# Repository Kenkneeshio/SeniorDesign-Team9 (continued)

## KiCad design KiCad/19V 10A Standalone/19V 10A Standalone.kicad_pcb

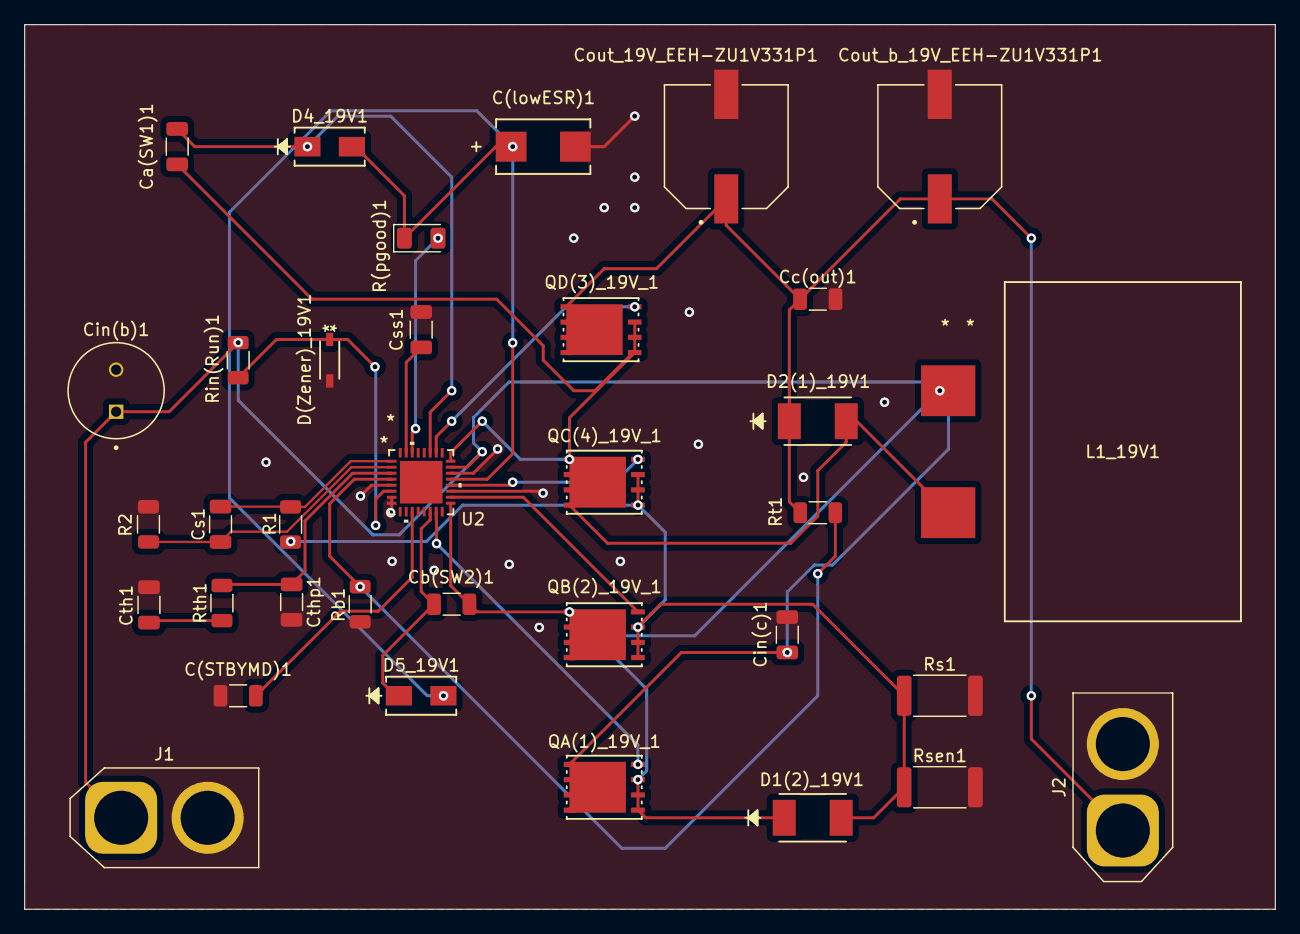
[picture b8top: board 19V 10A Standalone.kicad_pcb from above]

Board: 2 copper layers, 104.1 x 73.7 mm, 35 parts (0 on the bottom side), 22 nets.

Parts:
C(STBYMD)1: 0.001u; C_1206_3216Metric
C(lowESR)1: 4.7u; CAPMP7.6X4.3_3.1N_KEM
Ca(SW1)1: 0.22u; C_1206_3216Metric
Cb(SW2)1: 0.22u; C_1206_3216Metric
Cc(out)1: 47u; C_1206_3216Metric
Cin(b)1: 270u; LargeCAPSCAPPRD350W60D800H1200
Cin(c)1: 10u; C_1206_3216Metric
Cout_19V_EEH-ZU1V331P1: 330u; CAP_EEHZU1V331P
Cout_b_19V_EEH-ZU1V331P1: 330u; CAP_EEHZU1V331P
Cs1: 100p; C_1206_3216Metric
Css1: 0.001u; C_1206_3216Metric
Cth1: 10000p; C_1206_3216Metric
Cthp1: 47p; C_1206_3216Metric
D1(2)_19V1, D2(1)_19V1: SD2114S040S8R0; SD2114_AVX
D4_19V1, D5_19V1: D_Schottky_B340AE-13; CR_SMA_320-340AE_DIO
D(Zener)_19V1: D_Zener_BZT52C4V7-13-F; SOD123_DIO
J1: Conn_01x02_Socket; AMASS_XT60-M_1x02_P7.20mm_Vertical
J2: Conn_01x02_Socket; AMASS_XT60-F_1x02_P7.20mm_Vertical
L1_19V1: 6.8u Wurth 74436410680; IND_410680_WRE
QA(1)_19V_1: BSC009NE2LS5IATMA1; PG-TDSON-8_INF_modified_ken
QB(2)_19V_1: BSC009NE2LS5IATMA1; PG-TDSON-8_INF_modified_ken
QC(4)_19V_1: BSC009NE2LS5IATMA1; PG-TDSON-8_INF_modified_ken
QD(3)_19V_1: BSC009NE2LS5IATMA1; PG-TDSON-8_INF_modified_ken
R1, R2: 100; R_1206_3216Metric
R(pgood)1: 100k; LED_1206_3216Metric
Rb1: 4.3K; R_1206_3216Metric
Rin(Run)1: 51K; R_1206_3216Metric
Rs1: 6m; R_2512_6332Metric
Rsen1: 6m; R_2512_6332Metric
Rt1: 100K; R_1206_3216Metric
Rth1: 124K; R_1206_3216Metric
U2: LTC3780EUH-TRPBF; QFN-32_UH_LIT

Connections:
/BG1: QC(4)_19V_1.4, U2.20 (BG1)
/BG2: QB(2)_19V_1.4, U2.18 (BG2)
/BOOST1: Ca(SW1)1.1, D4_19V1.1 (K), U2.27 (BOOST1)
/BOOST2: Cb(SW2)1.2, D5_19V1.1 (K), U2.14 (BOOST2)
/INTVCC: C(lowESR)1.1, D4_19V1.2 (A), D5_19V1.2 (A), R(pgood)1.1, U2.21 (INTVCC)
/ITH: Cthp1.1, Rth1.2, U2.3 (ITH)
/PGOOD: R(pgood)1.2, U2.30 (PGOOD)
/Rsense: D1(2)_19V1.2, QB(2)_19V_1.1, QB(2)_19V_1.2, QB(2)_19V_1.3, QC(4)_19V_1.1, QC(4)_19V_1.2, QC(4)_19V_1.3, R1.1, Rs1.1, Rsen1.1
/Run: D(Zener)_19V1.1 (K), Rin(Run)1.2, U2.6 (RUN)
/SENSE+: Cs1.2, R1.2, U2.1 (SENSE+)
/SENSE-: Cs1.1, R2.1, U2.2 (SENSE-)
/SS: Css1.2, U2.31 (SS)
/STBYMD: C(STBYMD)1.1, U2.11 (STBYMD)
/SW1: Ca(SW1)1.2, D2(1)_19V1.2, L1_19V1.2, QC(4)_19V_1.5, QC(4)_19V_1.6, QC(4)_19V_1.7, QC(4)_19V_1.8, QD(3)_19V_1.1, QD(3)_19V_1.2, QD(3)_19V_1.3, U2.24 (SW1)
/SW2: Cb(SW2)1.1, D1(2)_19V1.1, L1_19V1.1, QA(1)_19V_1.1, QA(1)_19V_1.2, QA(1)_19V_1.3, QB(2)_19V_1.5, QB(2)_19V_1.6, QB(2)_19V_1.7, QB(2)_19V_1.8, U2.17 (SW2)
/TG1: QD(3)_19V_1.4, U2.26 (TG1)
/TG2: QA(1)_19V_1.4, U2.15 (TG2)
/VOSENSE: Rb1.1, Rt1.2, U2.4 (VOSENSE)
/Vin: Cin(b)1.1, Cin(c)1.1, J1.1, QA(1)_19V_1.5, QA(1)_19V_1.6, QA(1)_19V_1.7, QA(1)_19V_1.8, Rin(Run)1.1, U2.23 (VIN)
/Vout: Cc(out)1.1, Cout_19V_EEH-ZU1V331P1.1, Cout_b_19V_EEH-ZU1V331P1.1, D2(1)_19V1.1, J2.1, QD(3)_19V_1.5, QD(3)_19V_1.6, QD(3)_19V_1.7, QD(3)_19V_1.8, Rt1.1
GND: C(STBYMD)1.2, C(lowESR)1.2, Cc(out)1.2, Cin(b)1.2, Cin(c)1.2, Cout_19V_EEH-ZU1V331P1.2, Cout_b_19V_EEH-ZU1V331P1.2, Css1.1, Cth1.2, Cthp1.2, D(Zener)_19V1.2 (A), J1.2, J2.2, R2.2, Rb1.2, Rs1.2, Rsen1.2, U2.5 (SGND), U2.7 (FCB), U2.8 (PLLFLTR), U2.19 (PGND), U2.22 (EXTVCC)
unnamed: Cth1.1, Rth1.1

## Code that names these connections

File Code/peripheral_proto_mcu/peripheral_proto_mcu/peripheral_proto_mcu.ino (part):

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#include <OneWire.h>           // used for temperature sensor one wire
#include <DallasTemperature.h> // temperature sensor library

#define ONE_WIRE_BUS 5 // THE DIGITAL PIN THAT THE TEMPERATURE SENSORS ARE CONNECTED TO
//////////////////////////////
// FINAL BOARD PINS
#define VOLTAGE0_PIN A0
#define VOLTAGE1_PIN A1
#define CURRENT0_PIN A2
#define CURRENT1_PIN A3
/////////////////////////////

//////////////////////////////
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// #define VOLTAGE0_PIN A0
// #define VOLTAGE1_PIN A2
// #define CURRENT0_PIN A1
// #define CURRENT1_PIN A3
/////////////////////////////

//////////////////////////////////////////////////////////
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
  if (millis() > millis_ctr)
  {
    presentCurrent0 = ADC2Current(analogRead(CURRENT0_PIN));    // read analog value from adc, and pass to ADC2Current to convert into a real current
    presentVoltage0 = ADC2Voltage(analogRead(VOLTAGE0_PIN), 1); // read analog value from adc, and pass to ADC2Voltage to convert into a real voltage
    presentCurrent1 = ADC2Current(analogRead(CURRENT1_PIN));    // read analog value from adc, and pass to ADC2Current to convert into a real current
    presentVoltage1 = ADC2Voltage(analogRead(VOLTAGE1_PIN), 2); // read analog value from adc, and pass to ADC2Voltage to convert into a real voltage
    
    CollectTemperatureInformation();                            // call the temperature collecting function
    CheckBattery1Voltage(millis_ctr);                           // call the function to check battery one's health
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
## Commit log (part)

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2023-05-06 cleanup
2023-05-06 gitignore zip
2023-05-06 test
2023-05-12 .zip??
2023-05-12 gitignore
2023-05-12 Add MCU to the root Kicad
2023-05-12 Fixed 5V reg footprint
2023-05-12 Add Note for +5V label on 5V Buck
2023-05-12 5V Buck Schematic and Some Components
2023-05-12 Updfates
2023-05-12 Net listed and attacked outline components
2023-05-12 Changed footprints on my end only
2023-05-12 update for layout before 1 H break
2023-05-13 Layout Updates
2023-05-13 VIA FUN
2023-05-13 Load Sharing Traces
2023-05-13 Fixed Footprint/Symbol Paths and 19V Boost Footprint
2023-05-13 so many updates
2023-05-13 All Footprints Load from Mechatronics Folder
2023-05-13 My Load Sharing Group
2023-05-13 LTPowerCad files with BSC009NE2LS5I on all mosfets
    BSC009NE2LS5I
2023-05-14 Completed Load Sharing Circuit PCB
2023-05-14 Deleted 12 and 5 V. 19V updated
2023-05-14 Corrceted 19V components
2023-05-14 Fully Updated 19V SCh
2023-05-14 Added Voltmeter
2023-05-14 Major Changes
2023-05-14 Repaired root grid
2023-05-14 Repaired Grid root
2023-05-14 fixed SW1
2023-05-14 updated footprints
2023-05-14 Added ground planes to 19V
2023-05-14 Changed the Diodes
2023-05-14 19V Update
2023-05-14 Completed 19V
2023-05-14 Revisions before sleep
2023-05-14 Microcontroller Traces
2023-05-14 mcu ground plane
2023-05-15 Deleted Current Sense Circuit to remove errors and started 5V system
2023-05-15 Removed all Electrical Errors from PCB File...Moving on to add 5V System
2023-05-15 footprints
2023-05-15 Corrected all footprint errors and PCB electrical errors......NOW onto the 5V
2023-05-15 Added prototype 12V and 5V boards
2023-05-15 12 and 5 continued
2023-05-15 LABEL
2023-05-15 Updated the Footprints
2023-05-15 WIRE X
2023-05-15 Fixing 5V Problems
2023-05-15 5V updates
2023-05-15 More fix
2023-05-15 Fixed a bunch of unconnected connections on all the sheets Schematics
2023-05-15 Corrected Planess
2023-05-15 Placed the components. Only thing left is to Connect all the connections of the 12 and 5v bucks
2023-05-15 Completed V0 of the PCB....except the zener diodes need to change due to stock
2023-05-15 Completed First Prototype!!!!!!!
2023-06-13 EEHZU1V331P 330uF NMOS
    Added the schematic and footprint for the correct 330uF Cap
2023-06-13 Changed to CAP
2023-06-14 328pb to 328p
2023-06-14 19V 10A Boost Converter
    This should be the new PCB for the updated IC since the OG one is out of stock.
2023-06-21 19V 10A Standalone PCB
    Updated the standalone 19V 10A PCB. Just needs the connectors.
2023-06-23 19V 10A Standalone PCB
    Final design of the Boost converter should be finished, double check if possible please!
2023-06-24 Current Sense Standalone PCB
    Added the KiCad Schematic/PCB to the RPS01 folder
2023-06-24 Current Sense
    Updated schematic
2023-06-24 Update 19V 10A Standalone.kicad_pcb
    Fixed Ground planes
2023-06-24 fixzed super bad issue on ground plane
2023-06-24 solid vs thermal ground planes
2023-06-24 updated Current sense circuit
2023-06-24 Current Circuit setup.
2023-06-24 Organized Folder
2023-06-24 datahseets
2023-06-24 Current Sense Update
    Added cap filter
2023-06-26 100kohm load resistor
    Added 100kohm load resistor symbol and footprint for the current sense.
2023-06-26 Current Sense Update
    Updated footprints for the headers. Just waiting on which capacitors we will use.
2023-06-26 New Update
2023-06-27 Current Sense
    Updated PCB and Gerber Files
2023-06-27 Boost Converter
    Added Gerber Files
2023-06-27 Zipped Gerber Files
2023-06-28 ADR symbol and footprint
2023-07-06 Current Sense Update
2023-08-22 import fuse to schematic and add temp sensor jst header
2023-08-23 began pcb rework
2023-08-23 Updated Current Sense Standalone
    new footprint for R_SENSE and fixed header pins
2023-08-24 add fuse footprints
2023-08-24 Mill Current Sense PCB
2023-08-26 Made traces a bit thicker for current sense
2023-08-29 tweaked traces
2023-08-29 [internal screaming]
2023-08-30 Fuse test circuit and updated current sense
2023-08-31 Current Sense (High Current)
    Made a copy of the current sense KiCad file to implement for high current.
2023-08-31 added sweep
2023-08-31 200AMP Sweep
2023-08-31 rearranged schematic for current sense
2023-08-31 Current Sense Dimensions
    Adjusted dimensions of the width and length of the board. Still in-progress with the components.
2023-09-02 Resume Builder - Jaxon
2023-09-02 MCU Single side board
2023-09-04 Current Sense (High Current)
    Fixed plane connections
2023-09-05 Add Current Sense to RPS01
2023-09-05 Add Fuses and other ADC pin
2023-09-06 Code
2023-09-06 Current Sense Gerber and Drill Files (9-6-23)
2023-09-07 added rails and sensors
2023-09-07 Update G code
2023-09-07 Add Serial Number grabber code, update serial numbers
2023-09-07 Updated Layout
2023-09-07 PCB Update
2023-09-07 PCB Updates
2023-09-07 THT to SMD
2023-09-07 update pcb
2023-09-07 PCB and added second ESC Output
2023-09-07 Updated PCB
2023-09-07 updated shunt resistor
2023-09-07 Start Demo code for devices
2023-09-07 create master and slave code
2023-09-08 Temperature reading is sort of working
2023-09-08 fixed temperature code
2023-09-08 Buck Converter
2023-09-08 More
2023-09-08 added 3d models
2023-09-08 Added Models
2023-09-08 1206 to 0603
2023-09-09 Huge PCB Update
2023-09-09 Fixed Plane
2023-09-09 Finished Load Sharing and Current Sense
2023-09-09 MCU Changes
2023-09-09 Added Screen to MCU
2023-09-10 LLC schematic
2023-09-10 4.7K R
2023-09-10 fix LLC and add temperature sensor page
2023-09-10 updated MCU
2023-09-10 Large Schematic Update
2023-09-10 Huge Schematic Update
2023-09-10 Finished most of the Schematics. Needs polishing
2023-09-10 Finished Updating Footprints and Reorganized Reference Designators
    Finished Updating Footprints and Reorganized Reference Designators
    Starting to work on Final PCB, except for 19V Boost. Please check Schematic for errors
2023-09-10 minor update
2023-09-10 add resistor and cap values for buck
2023-09-10 add 19v boost from other ver
2023-09-11 Board Ready For layout. Except for 19V Boost? CHECK vs SIM Please
    Board Ready For layout. Except for 19V Boost? CHECK vs SIM Please
2023-09-11 Hotfix
2023-09-11 progress
2023-09-11 Last Update before HW Break
2023-09-11 move resistor labels and add models
2023-09-11 Getting THERE. ALMOST THERE
2023-09-11 Completed Logic Stuff. Only Voltage Rail Stuff to Finish
    Completed Logic Stuff. Only Voltage Rail Stuff to Finish
2023-09-11 Dimensioned PCB
2023-09-11 Fix Dimensions
2023-09-11 Finished everything but test points and 19V Buck/Boost
2023-09-11 changed ltc3780 to the small one
2023-09-11 Error Checker Complete
2023-09-12 Added Proper Mounting Holes and Updated PCB Dimensions
2023-09-12 Fixed Thermal and Current Vias
2023-09-12 Rounded the Corners to the PCB
2023-09-12 TODO: Some minor DRC Fixes, SILKSCREEN LABELS, MASK GRAPHICS
2023-09-12 Fix labels and add graphics
2023-09-13 add jason signature and fix resistor footprint
2023-09-13 fix 330uF labels
2023-09-13 extra
2023-09-13 add V+ filter caps to current sense schematic
2023-09-13 update step file and 3d pcb
2023-09-13 update render
2023-09-14 add secondary voltage current sensing
2023-09-15 RGB——board
2023-09-15 measure
2023-09-15 LED code
2023-09-15 Updated Caps
2023-09-15 fixed errors
2023-09-15 push check
2023-09-15 update probe text and start fuse model
2023-09-15 code / rgb cnc / enable simulation
2023-09-16 Plane
2023-09-17 update some graphics
2023-09-17 Fixed Ignore List
2023-09-17 document some code
2023-09-17 Ready For JLC
2023-09-17 Double Check
2023-09-17 Fixed and mention error on R1 Board
2023-09-17 added xt30 models
2023-09-17 Does pictures save?
2023-09-17 added xt30 steps
2023-09-21 edit some mcu code
2023-09-21 Current Sense Rails C_22 from 80p to 0.1u
2023-09-22 Mech Drawings
2023-09-22 add art
2023-09-22 3d models
2023-09-22 Added the Plastic top
2023-09-22 update renders and change xt30 models
2023-09-22 add some more diagrams
2023-09-22 add acrylic part
2023-09-24 update some code
2023-09-26 update some rgb codes and led pinouts
2023-09-26 clean up code, and add more comments
2023-09-27 changed adc pinout, more error checks
2023-09-27 Orange LED update
2023-09-27 ken update load sharing
2023-09-27 update load sharing enable
2023-09-27 change back enable
2023-09-28 Made rev 3 folder
2023-09-28 updated sims
2023-10-02 Created overvoltage sim
2023-10-03 added working screen code
2023-10-03 added simple code for screen
2023-10-04 update some peripheral code
2023-10-04 UPDATE BATTERY VOLT DIVIDER VALUES
2023-10-04 update renders
2023-10-04 update logic level volt and fix batt1/2 adc
2023-10-04 update top graphic
2023-10-05 fixed adc syntax, added NOP command
2023-10-07 fixed NOP commands and recognizing RESET
2023-10-12 adjust system command values
2023-10-12 LED update
2023-10-12 add ver 2 of peripheral
2023-10-12 ver 2 of peripheral is working
2023-10-14 update peripheral ver 2 and add some singular test code
2023-10-20 addded 3780 Info
2023-10-20 ypup
2023-10-21 test code for ADC current 1
2023-10-24 push code to match readiness report
2023-10-29 Updated Sim
2023-10-31 add current and battery linear regression
2023-11-01 LTC3780 Circuit Ken Updates
2023-11-01 Finished Schematic
2023-11-01 fixed errors. need footprints and PCB layout
2023-11-01 PCB Layout Started
2023-11-01 PCB Layout Continued
2023-11-01 LTC3780 Completed. PCB Ordered
2023-11-02 make temperature collecting faster
2023-11-02 Gain and offset added
2023-11-04 add new host code. Use this from now on!
2023-11-10 Temp gain offset update
2023-11-10 TEMP offset gain update
2023-11-14 Footprint and symbol for new regulators
2023-11-14 Add new LDO symbols (no footprint)
2023-11-14 add zener diodes
2023-11-15 add buffer sims and edit controller.ino
2023-11-16 Added LDO Diodes
2023-11-16 Updated Buffer, Precision LDO, new LDO
2023-11-16 Update LTC4416_Custom_Ken.asc
    Added pull-down resistors and MCU resistors
2023-11-16 Load Sharing
    Changed wiring for the reversed MOSFETs
2023-11-17 Add new inductor footprints
2023-11-17 update some references
2023-11-17 RPS-01 Rev 2 TP Silkscreen
    Added silkscreens to testpoints
2023-11-17 added 3780 Circuit
2023-11-17 Deleted a bunch of crap.
2023-11-17 Deleted SCreen
2023-11-17 Locking and clean. Prepare for Rework
2023-11-17 last schematic update for the night ken
2023-11-17 add 3.3v logic footprint (shouldn't be needed but incase)
2023-11-17 Update Microcontroller.kicad_sch
    Added pull-down resistors and fixed AVCC and VCC connections with filter cap.
2023-11-17 Update to sim
2023-11-17 Voltage rail update
2023-11-17 update volt sense diode refereneces
2023-11-17 Update Current sense references
2023-11-18 update led resistor and voltsense references
2023-11-18 Button Footprints
    Changed button footprints
2023-11-18 Update Rails.kicad_sch
    Added DNI to component values
2023-11-18 Updates to PCB
2023-11-18 zzzzzzzzzzzupdates
2023-11-18 saving
2023-11-18 traces for load sharing done
2023-11-18 revert Peter's changes
2023-11-18 Update Current Sense 2 shunt footprint
2023-11-18 Add Jumper for 3.3V Logic
2023-11-18 quick update
2023-11-18 Deleted one of the caps
2023-11-18 lOGIC POWER ALMOST DONE
2023-11-18 Push before Jason changes 3.3V
2023-11-18 Cap update 3.3V
2023-11-18 Only Switches left
2023-11-18 Completed everything except the 3780 and the Polishing
2023-11-18 Added 3780 and Fixed References
2023-11-18 Revert "Added 3780 and Fixed References"
    This reverts commit 85c2587d5771b26bef1ebaba5f57b8bbd8599db1.
2023-11-18 Prepare merge
2023-11-18 uploaded 3780? Might have to revert.
2023-11-19 Updated nets of Current 2 output and 3780 Globals.
2023-11-20 Fixed many Errors on Schematic
2023-11-20 Updated some MCU
2023-11-20 RPS01-Rev2 Silkscreen
2023-11-20 Update Ref
2023-11-20 Reduced the References for Peter
2023-11-20 Completed Schematic
2023-11-20 Updated for Peter
2023-11-20 Silkscreen update on PCB
2023-11-20 Fixes some errors
2023-11-20 Finished PCB
2023-11-20 update silkscreen
    add notes for pinouts and sectioned regions
2023-11-20 remove signatures from symbol
2023-11-21 Added Thermal Vias and Isolated Shunt Sense
2023-11-21 bom and pos files
2023-11-21 gerbers and brendan changes
2023-12-01 serial number added
2023-12-01 create revision2 peripheral code
2023-12-06 final update
2023-12-06 disable debug and change volt sense range
2023-12-10 fixes traces
